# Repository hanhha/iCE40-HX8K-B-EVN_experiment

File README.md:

# iCE40-HX8K-B-EVN_experiment
Collection of expansion PCB designs and documents that I created when playing with this board.

* HX8K_exp: expansion board that add 2 PMOD ports and a 64 pin socket.
* AS6C4008_32b: additional board that plug into 64 pin socket to add 4xAS6C4008 SRAM chip (DIP package).
* 8bDAC: Extension board to plug in J2 socket that provide a 8 bit R-2R network and some pinout (that I use to display stuff on a NTSC TV). 
* Documents: some documents.

### Expansion boards

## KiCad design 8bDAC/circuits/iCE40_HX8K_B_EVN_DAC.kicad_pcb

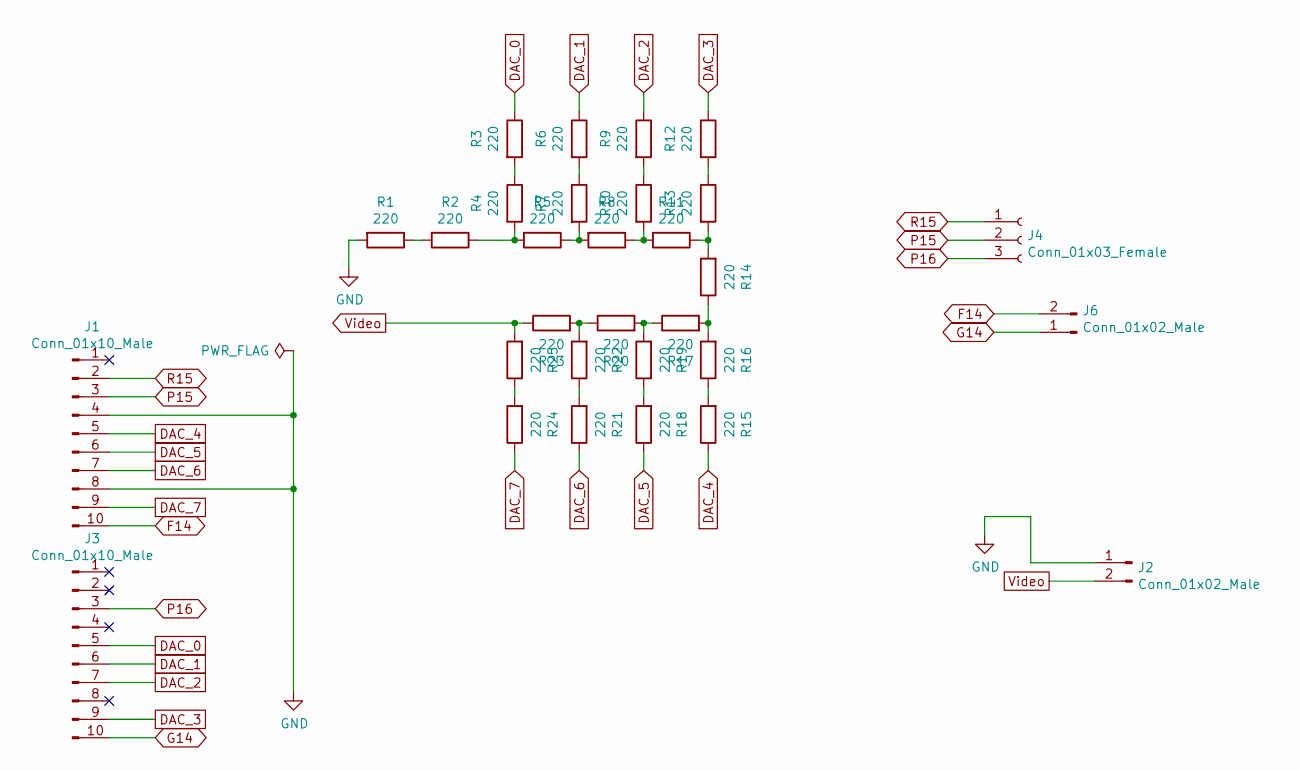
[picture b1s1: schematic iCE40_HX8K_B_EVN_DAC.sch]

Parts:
J1, J3: Conn_01x10_Male; PinHeader_1x10_P2.54mm_Vertical
J2, J6: Conn_01x02_Male; PinHeader_1x02_P2.54mm_Vertical
J4: Conn_01x03_Female; PinHeader_1x03_P2.54mm_Vertical
R1, R2, R3, R4, R5, R6, R7, R8, R9, R10, R11, R12, R13, R14, R15, R16, R17, R18, R19, R20, R21, R22, R23, R24, R25: 220; R_Axial_DIN0204_L3.6mm_D1.6mm_P7.62mm_Horizontal

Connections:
DAC_0: J3.5, R3.1
DAC_1: J3.6, R6.1
DAC_2: J3.7, R9.1
DAC_3: J3.9, R12.1
DAC_4: J1.5, R15.1
DAC_5: J1.6, R18.1
DAC_6: J1.7, R21.1
DAC_7: J1.9, R24.1
F14: J1.10, J6.2
G14: J3.10, J6.1
GND: J1.4, J1.8, J2.1, R1.2
unnamed: R1.1, R2.2
unnamed: R2.1, R4.2, R5.2
unnamed: R3.2, R4.1
unnamed: R5.1, R7.2, R8.2
unnamed: R6.2, R7.1
unnamed: R9.2, R10.1
unnamed: R8.1, R10.2, R11.2
unnamed: R11.1, R13.2, R14.2
unnamed: R12.2, R13.1
unnamed: R14.1, R16.2, R17.2
unnamed: R15.2, R16.1
unnamed: R17.1, R19.2, R20.2
unnamed: R18.2, R19.1
unnamed: R20.1, R22.2, R23.2
unnamed: R21.2, R22.1
unnamed: R24.2, R25.1
P15: J1.3, J4.2
P16: J3.3, J4.3
R15: J1.2, J4.1
Video: J2.2, R23.1, R25.2

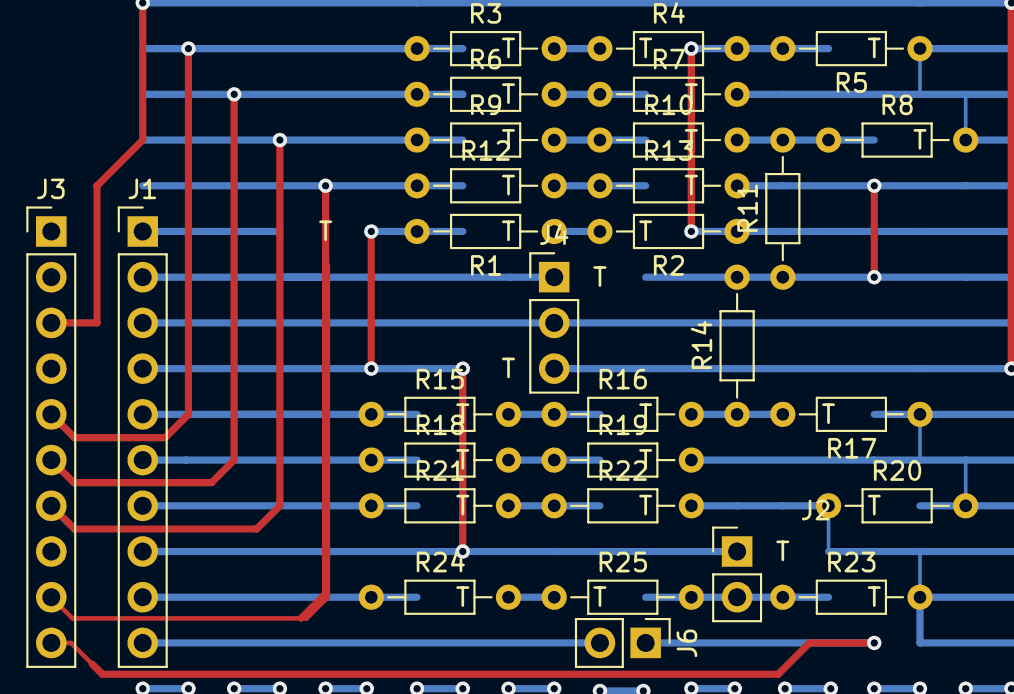
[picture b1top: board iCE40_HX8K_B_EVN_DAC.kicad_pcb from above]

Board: 2 copper layers, 30 parts (0 on the bottom side), 31 nets.

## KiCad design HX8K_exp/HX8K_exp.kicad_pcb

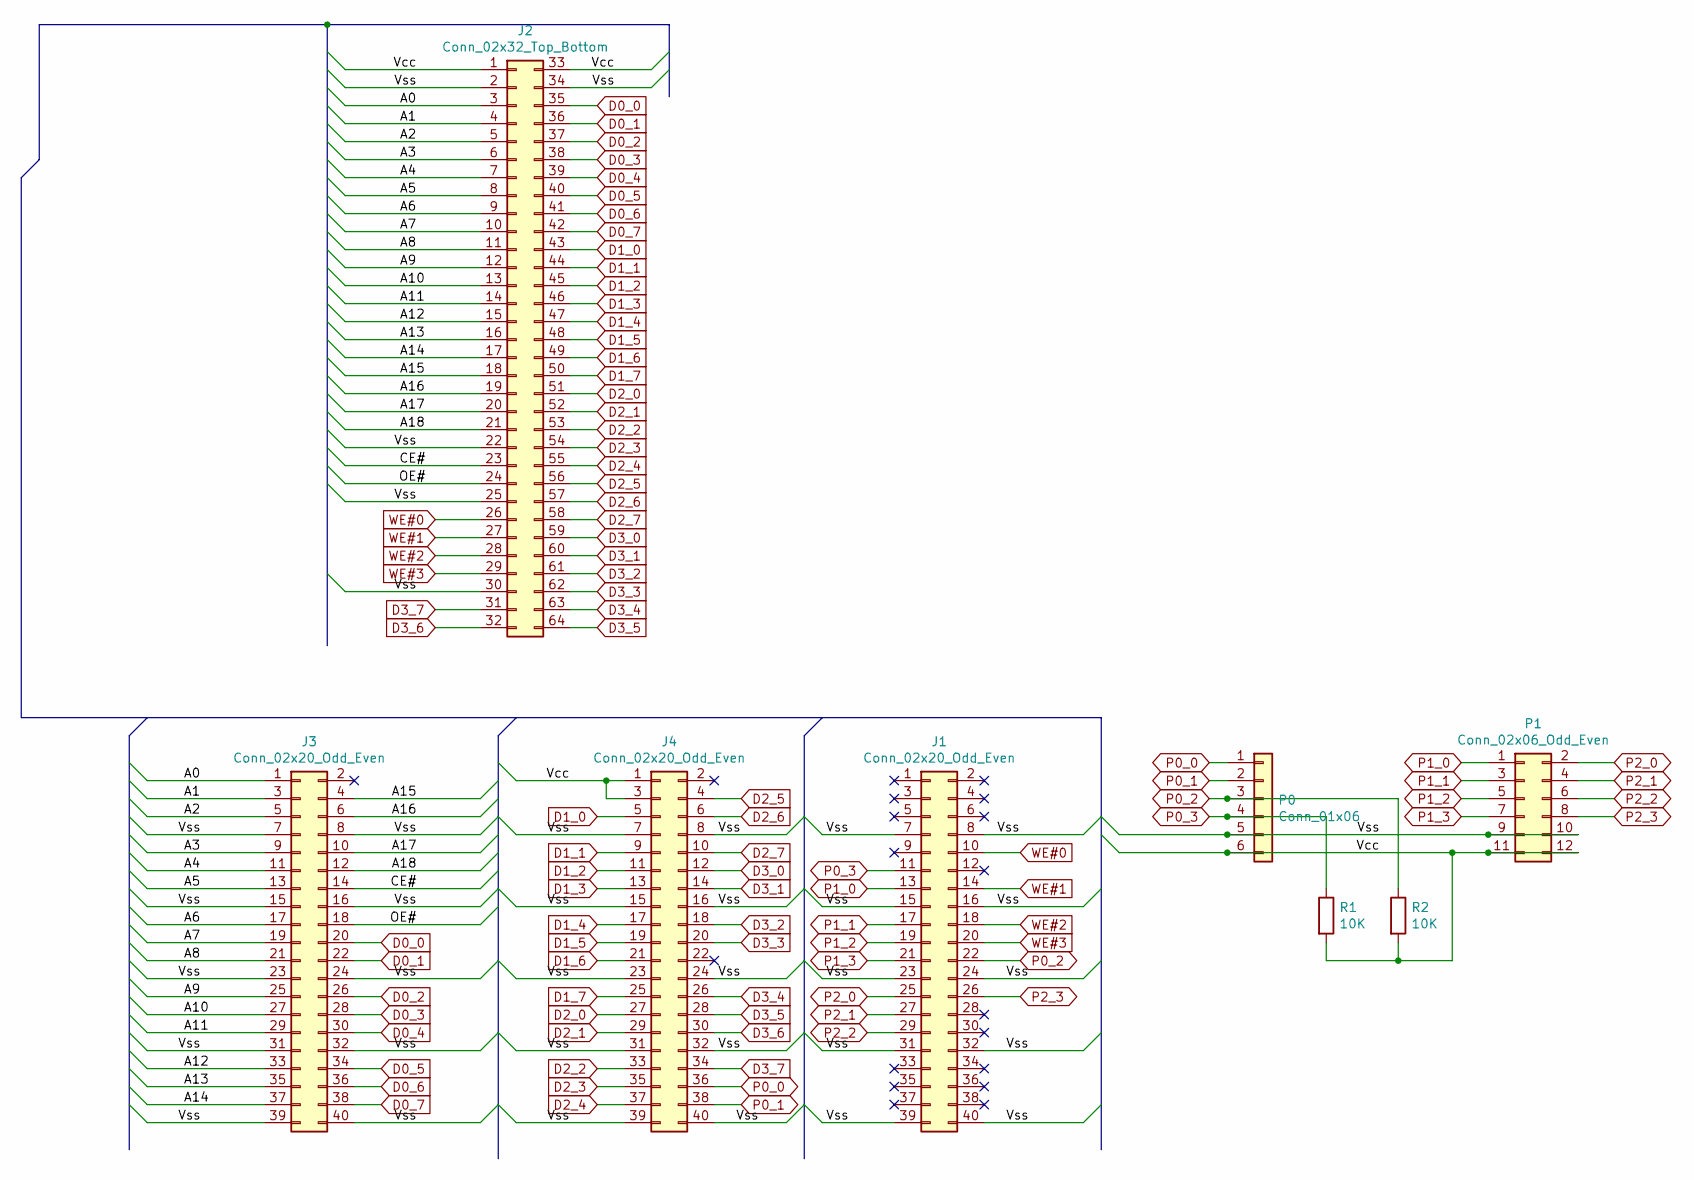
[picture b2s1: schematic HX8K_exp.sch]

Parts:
J1, J3, J4: Conn_02x20_Odd_Even; PinHeader_2x20_P2.54mm_Vertical
J2: Conn_02x32_Top_Bottom; PinSocket_2x32_P2.54mm_Vertical_Top_Bot_cartridge
P0: Conn_01x06; PinHeader_1x06_P2.54mm_Vertical
P1: Conn_02x06_Odd_Even; PinHeader_2x06_P2.54mm_Vertical
R1, R2: 10K; R_Axial_DIN0207_L6.3mm_D2.5mm_P7.62mm_Horizontal

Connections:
/A0: J2.3, J3.1
/A1: J2.4, J3.3
/A2: J2.5, J3.5
/A3: J2.6, J3.9
/A4: J2.7, J3.11
/A5: J2.8, J3.13
/A6: J2.9, J3.17
/A7: J2.10, J3.19
/A8: J2.11, J3.21
/A9: J2.12, J3.25
/A10: J2.13, J3.27
/A11: J2.14, J3.29
/A12: J2.15, J3.33
/A13: J2.16, J3.35
/A14: J2.17, J3.37
/A15: J2.18, J3.4
/A16: J2.19, J3.6
/A17: J2.20, J3.10
/A18: J2.21, J3.12
/CE#: J2.23, J3.14
/OE#: J2.24, J3.18
/Vcc: J2.1, J2.33, J4.1, J4.3, P0.6, P1.11, P1.12, R1.2, R2.2
/Vss: J1.7, J1.8, J1.15, J1.16, J1.23, J1.24, J1.31, J1.32, J1.39, J1.40, J2.2, J2.22, J2.25, J2.30, J2.34, J3.7, J3.8, J3.15, J3.16, J3.23, J3.24, J3.31, J3.32, J3.39, J3.40, J4.7, J4.8, J4.15, J4.16, J4.23, J4.24, J4.31, J4.32, J4.39, J4.40, P0.5, P1.9, P1.10
D0_0: J2.35, J3.20
D0_1: J2.36, J3.22
D0_2: J2.37, J3.26
D0_3: J2.38, J3.28
D0_4: J2.39, J3.30
D0_5: J2.40, J3.34
D0_6: J2.41, J3.36
D0_7: J2.42, J3.38
D1_0: J2.43, J4.5
D1_1: J2.44, J4.9
D1_2: J2.45, J4.11
D1_3: J2.46, J4.13
D1_4: J2.47, J4.17
D1_5: J2.48, J4.19
D1_6: J2.49, J4.21
D1_7: J2.50, J4.25
D2_0: J2.51, J4.27
D2_1: J2.52, J4.29
D2_2: J2.53, J4.33
D2_3: J2.54, J4.35
D2_4: J2.55, J4.37
D2_5: J2.56, J4.4
D2_6: J2.57, J4.6
D2_7: J2.58, J4.10
D3_0: J2.59, J4.12
D3_1: J2.60, J4.14
D3_2: J2.61, J4.18
D3_3: J2.62, J4.20
D3_4: J2.63, J4.26
D3_5: J2.64, J4.28
D3_6: J2.32, J4.30
D3_7: J2.31, J4.34
P0_0: J4.36, P0.1
P0_1: J4.38, P0.2
P0_2: J1.22, P0.3, R2.1
P0_3: J1.11, P0.4, R1.1
P1_0: J1.13, P1.1
P1_1: J1.17, P1.3
P1_2: J1.19, P1.5
P1_3: J1.21, P1.7
P2_0: J1.25, P1.2
P2_1: J1.27, P1.4
P2_2: J1.29, P1.6
P2_3: J1.26, P1.8
WE#0: J1.10, J2.26
WE#1: J1.14, J2.27
WE#2: J1.18, J2.28
WE#3: J1.20, J2.29

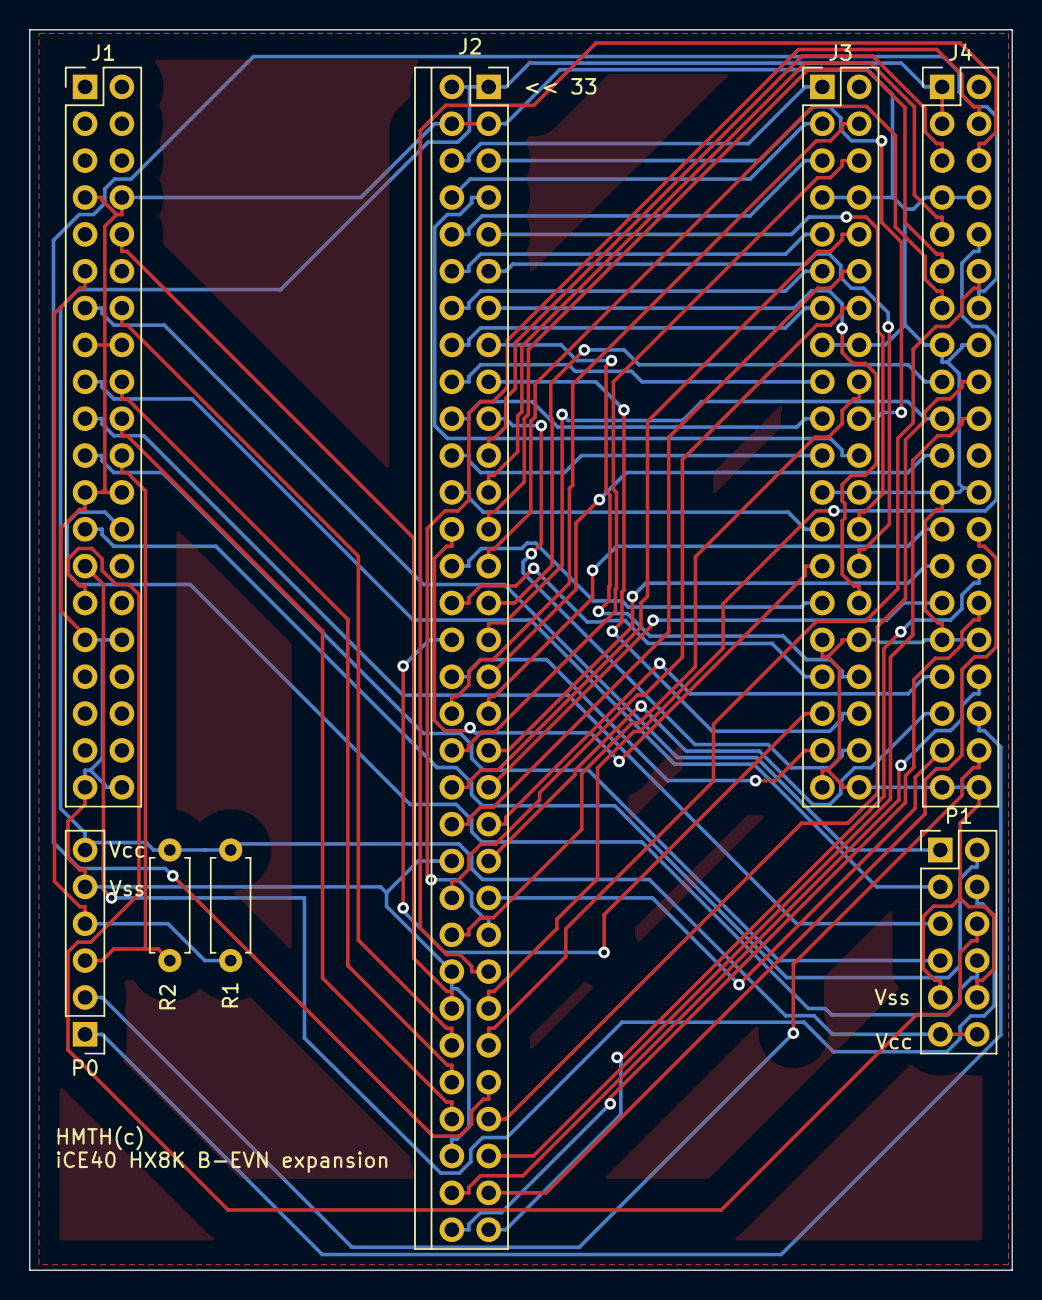
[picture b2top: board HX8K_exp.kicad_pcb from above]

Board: 2 copper layers, 67.7 x 85.5 mm, 8 parts (0 on the bottom side), 71 nets.

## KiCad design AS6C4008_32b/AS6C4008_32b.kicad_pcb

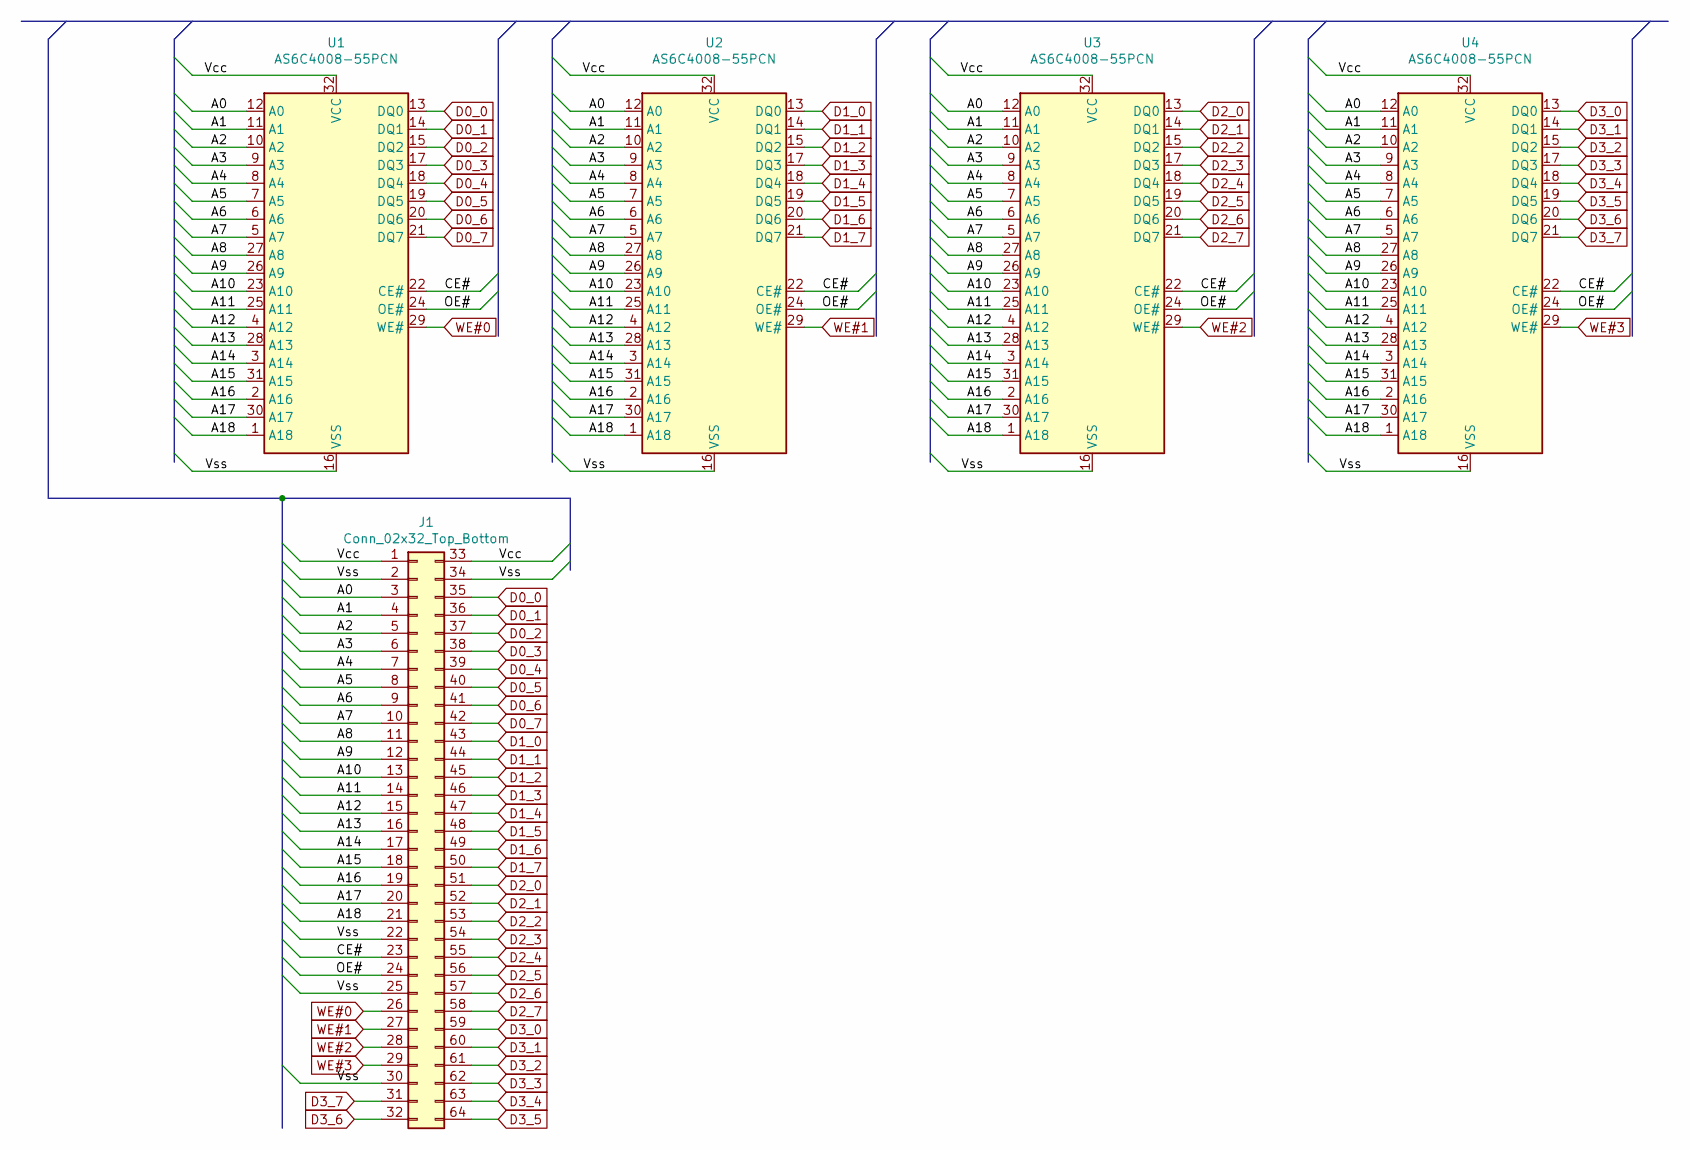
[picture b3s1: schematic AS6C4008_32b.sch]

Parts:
J1: Conn_02x32_Top_Bottom; PinHeader_2x32_P2.54mm_top_bottom_cartridge
U1, U2, U3, U4: AS6C4008-55PCN; DIP-32_W15.24mm

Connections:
/A0: J1.3, U1.12 (A0), U2.12 (A0), U3.12 (A0), U4.12 (A0)
/A1: J1.4, U1.11 (A1), U2.11 (A1), U3.11 (A1), U4.11 (A1)
/A2: J1.5, U1.10 (A2), U2.10 (A2), U3.10 (A2), U4.10 (A2)
/A3: J1.6, U1.9 (A3), U2.9 (A3), U3.9 (A3), U4.9 (A3)
/A4: J1.7, U1.8 (A4), U2.8 (A4), U3.8 (A4), U4.8 (A4)
/A5: J1.8, U1.7 (A5), U2.7 (A5), U3.7 (A5), U4.7 (A5)
/A6: J1.9, U1.6 (A6), U2.6 (A6), U3.6 (A6), U4.6 (A6)
/A7: J1.10, U1.5 (A7), U2.5 (A7), U3.5 (A7), U4.5 (A7)
/A8: J1.11, U1.27 (A8), U2.27 (A8), U3.27 (A8), U4.27 (A8)
/A9: J1.12, U1.26 (A9), U2.26 (A9), U3.26 (A9), U4.26 (A9)
/A10: J1.13, U1.23 (A10), U2.23 (A10), U3.23 (A10), U4.23 (A10)
/A11: J1.14, U1.25 (A11), U2.25 (A11), U3.25 (A11), U4.25 (A11)
/A12: J1.15, U1.4 (A12), U2.4 (A12), U3.4 (A12), U4.4 (A12)
/A13: J1.16, U1.28 (A13), U2.28 (A13), U3.28 (A13), U4.28 (A13)
/A14: J1.17, U1.3 (A14), U2.3 (A14), U3.3 (A14), U4.3 (A14)
/A15: J1.18, U1.31 (A15), U2.31 (A15), U3.31 (A15), U4.31 (A15)
/A16: J1.19, U1.2 (A16), U2.2 (A16), U3.2 (A16), U4.2 (A16)
/A17: J1.20, U1.30 (A17), U2.30 (A17), U3.30 (A17), U4.30 (A17)
/A18: J1.21, U1.1 (A18), U2.1 (A18), U3.1 (A18), U4.1 (A18)
/CE#: J1.23, U1.22 (CE#), U2.22 (CE#), U3.22 (CE#), U4.22 (CE#)
/OE#: J1.24, U1.24 (OE#), U2.24 (OE#), U3.24 (OE#), U4.24 (OE#)
/Vcc: J1.1, J1.33, U1.32 (VCC), U2.32 (VCC), U3.32 (VCC), U4.32 (VCC)
/Vss: J1.2, J1.22, J1.25, J1.30, J1.34, U1.16 (VSS), U2.16 (VSS), U3.16 (VSS), U4.16 (VSS)
D0_0: J1.35, U1.13 (DQ0)
D0_1: J1.36, U1.14 (DQ1)
D0_2: J1.37, U1.15 (DQ2)
D0_3: J1.38, U1.17 (DQ3)
D0_4: J1.39, U1.18 (DQ4)
D0_5: J1.40, U1.19 (DQ5)
D0_6: J1.41, U1.20 (DQ6)
D0_7: J1.42, U1.21 (DQ7)
D1_0: J1.43, U2.13 (DQ0)
D1_1: J1.44, U2.14 (DQ1)
D1_2: J1.45, U2.15 (DQ2)
D1_3: J1.46, U2.17 (DQ3)
D1_4: J1.47, U2.18 (DQ4)
D1_5: J1.48, U2.19 (DQ5)
D1_6: J1.49, U2.20 (DQ6)
D1_7: J1.50, U2.21 (DQ7)
D2_0: J1.51, U3.13 (DQ0)
D2_1: J1.52, U3.14 (DQ1)
D2_2: J1.53, U3.15 (DQ2)
D2_3: J1.54, U3.17 (DQ3)
D2_4: J1.55, U3.18 (DQ4)
D2_5: J1.56, U3.19 (DQ5)
D2_6: J1.57, U3.20 (DQ6)
D2_7: J1.58, U3.21 (DQ7)
D3_0: J1.59, U4.13 (DQ0)
D3_1: J1.60, U4.14 (DQ1)
D3_2: J1.61, U4.15 (DQ2)
D3_3: J1.62, U4.17 (DQ3)
D3_4: J1.63, U4.18 (DQ4)
D3_5: J1.64, U4.19 (DQ5)
D3_6: J1.32, U4.20 (DQ6)
D3_7: J1.31, U4.21 (DQ7)
WE#0: J1.26, U1.29 (WE#)
WE#1: J1.27, U2.29 (WE#)
WE#2: J1.28, U3.29 (WE#)
WE#3: J1.29, U4.29 (WE#)

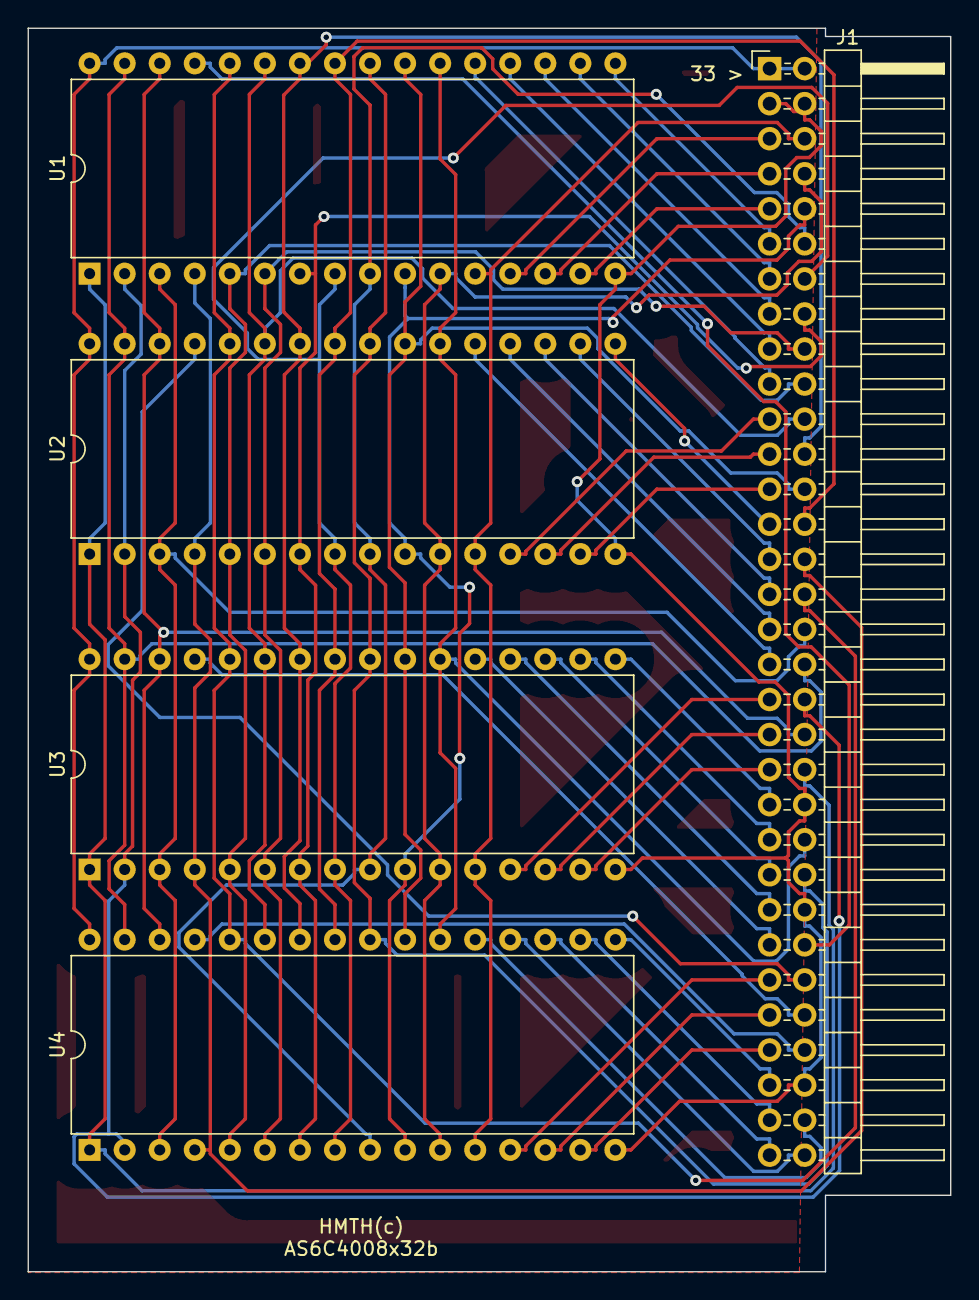
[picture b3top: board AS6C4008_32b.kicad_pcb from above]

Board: 2 copper layers, 66.8 x 90.1 mm, 5 parts (0 on the bottom side), 59 nets.

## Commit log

2020-01-12 Add DAC board
